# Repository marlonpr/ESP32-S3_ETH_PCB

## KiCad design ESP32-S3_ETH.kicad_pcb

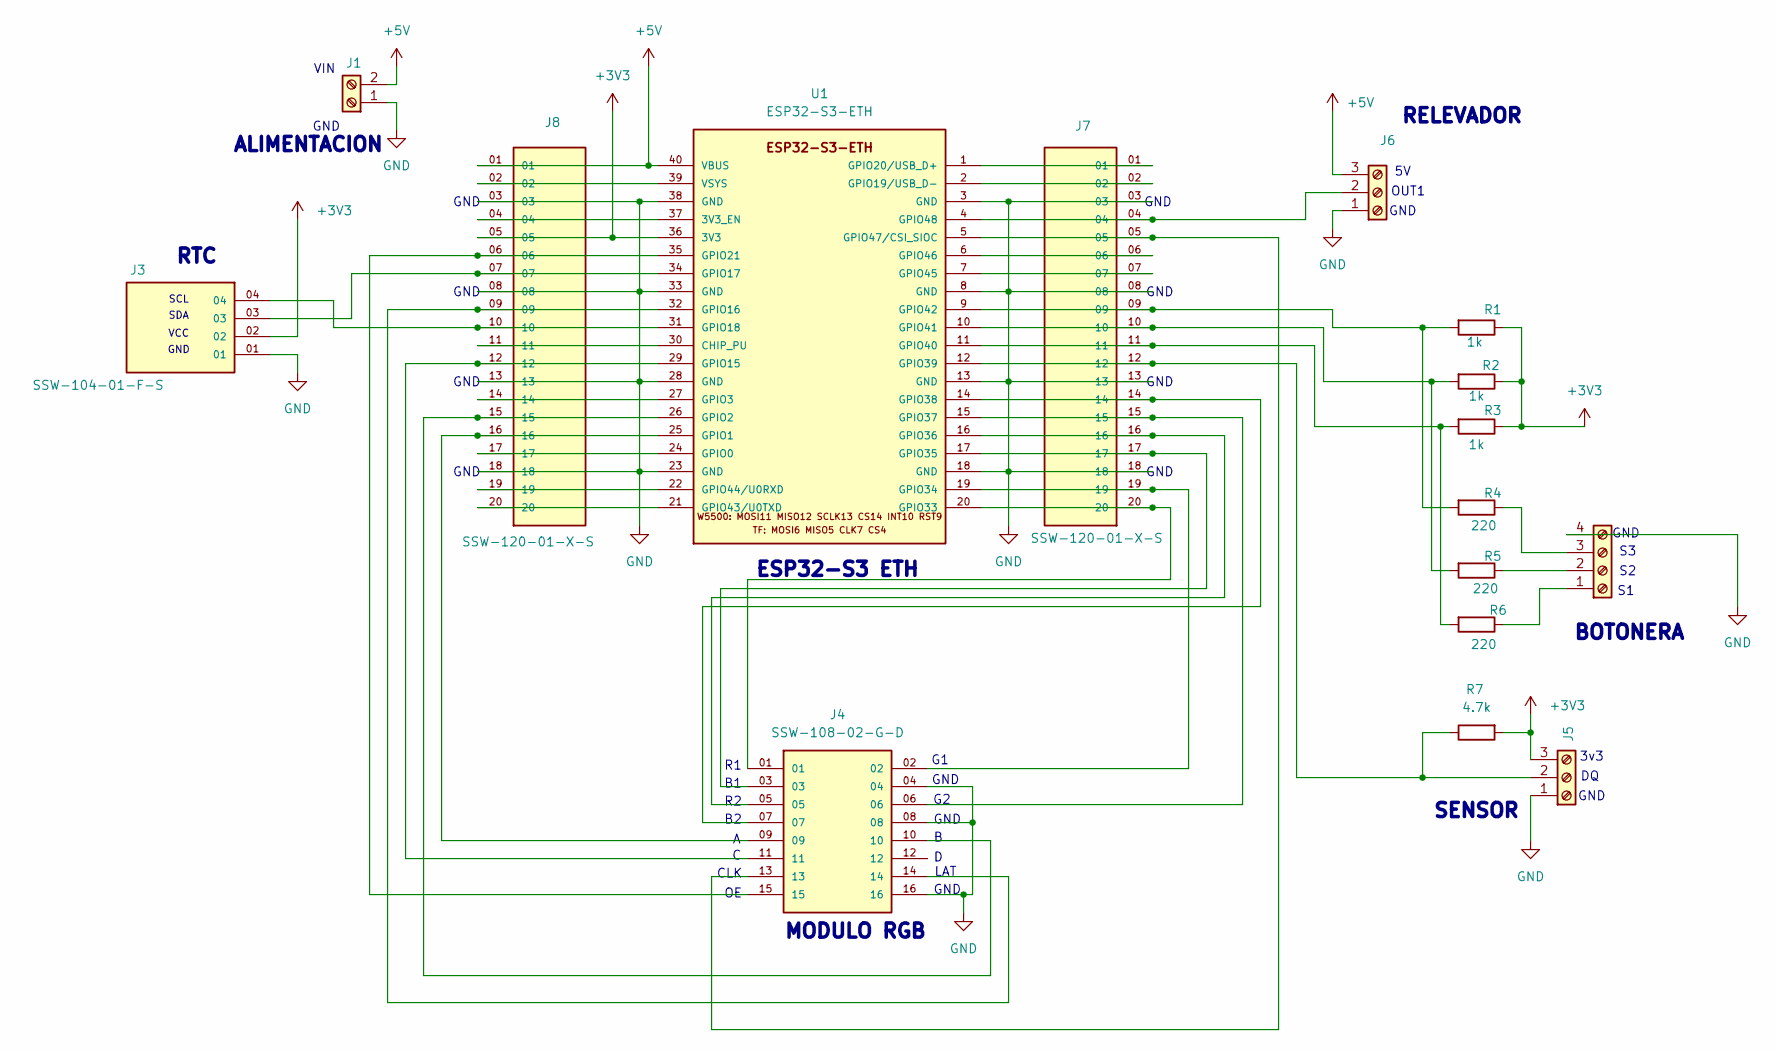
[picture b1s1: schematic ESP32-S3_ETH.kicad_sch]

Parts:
J1: Screw_Terminal_01x02; TerminalBlock_Altech_AK300-2_P5.00mm
J2: Screw_Terminal_01x04; TerminalBlock_Altech_AK300-4_P5.00mm
J3: SSW-104-01-F-S; SAMTEC_SSW-104-01-F-S-RTC; PARTREV R
J4: SSW-108-02-G-D; SAMTEC_SSW-108-02-G-D
J5, J6: Screw_Terminal_01x03; TerminalBlock_Altech_AK300-3_P5.00mm
J7, J8: SSW-120-01-X-S; SAMTEC_SSW-120-01-X-S
R1, R2, R3: 1k; R_Axial_DIN0207_L6.3mm_D2.5mm_P7.62mm_Horizontal
R4, R5, R6: 220; R_Axial_DIN0207_L6.3mm_D2.5mm_P7.62mm_Horizontal
R7: 4.7k; R_Axial_DIN0207_L6.3mm_D2.5mm_P7.62mm_Horizontal
U1: ESP32-S3-ETH; MODULE_ESP32-S3-ETH

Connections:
+3V3: J3.02, J5.3, J8.05, R1.1, R2.1, R3.1, R7.2, U1.36 (3V3)
+5V: J1.2, J6.3, J8.01, U1.40 (VBUS)
GND: J1.1, J2.4, J3.01, J4.04, J4.08, J4.16, J5.1, J6.1, J7.03, J7.08, J7.13, J7.18, J8.03, J8.08, J8.13, J8.18, U1.3 (GND), U1.8 (GND), U1.13 (GND), U1.18 (GND), U1.23 (GND), U1.28 (GND), U1.33 (GND), U1.38 (GND)
unnamed: J2.1, R6.1
unnamed: J2.2, R5.1
unnamed: J2.3, R4.1
unnamed: J5.2, J7.12, R7.1, U1.12 (GPIO39)
unnamed: J6.2, J7.04, U1.4 (GPIO48)
unnamed: J8.04, U1.37 (3V3_EN)
unnamed: J8.11, U1.30 (CHIP_PU)
unnamed: J8.17, U1.24 (GPIO0)
unnamed: J4.09, J8.16, U1.25 (GPIO1)
unnamed: J4.10, J8.15, U1.26 (GPIO2)
unnamed: J8.14, U1.27 (GPIO3)
unnamed: J4.11, J8.12, U1.29 (GPIO15)
unnamed: J4.14, J8.09, U1.32 (GPIO16)
unnamed: J3.03, J8.07, U1.34 (GPIO17)
unnamed: J3.04, J8.10, U1.31 (GPIO18)
unnamed: J7.02, U1.2 (GPIO19/USB_D-)
unnamed: J7.01, U1.1 (GPIO20/USB_D+)
unnamed: J4.15, J8.06, U1.35 (GPIO21)
unnamed: J4.01, J7.20, U1.20 (GPIO33)
unnamed: J4.02, J7.19, U1.19 (GPIO34)
unnamed: J4.03, J7.17, U1.17 (GPIO35)
unnamed: J4.05, J7.16, U1.16 (GPIO36)
unnamed: J4.06, J7.15, U1.15 (GPIO37)
unnamed: J4.07, J7.14, U1.14 (GPIO38)
unnamed: J7.11, R3.2, R6.2, U1.11 (GPIO40)
unnamed: J7.10, R2.2, R5.2, U1.10 (GPIO41)
unnamed: J7.09, R1.2, R4.2, U1.9 (GPIO42)
unnamed: J8.20, U1.21 (GPIO43/U0TXD)
unnamed: J8.19, U1.22 (GPIO44/U0RXD)
unnamed: J7.07, U1.7 (GPIO45)
unnamed: J7.06, U1.6 (GPIO46)
unnamed: J4.13, J7.05, U1.5 (GPIO47/CSI_SIOC)
unnamed: J8.02, U1.39 (VSYS)

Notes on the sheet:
LAT
OUT1
GND
MODULO RGB
BOTONERA
CLK
VCC
SDA
VIN
ESP32-S3 ETH
RTC
ALIMENTACION
SENSOR
RELEVADOR
SCL
3v3

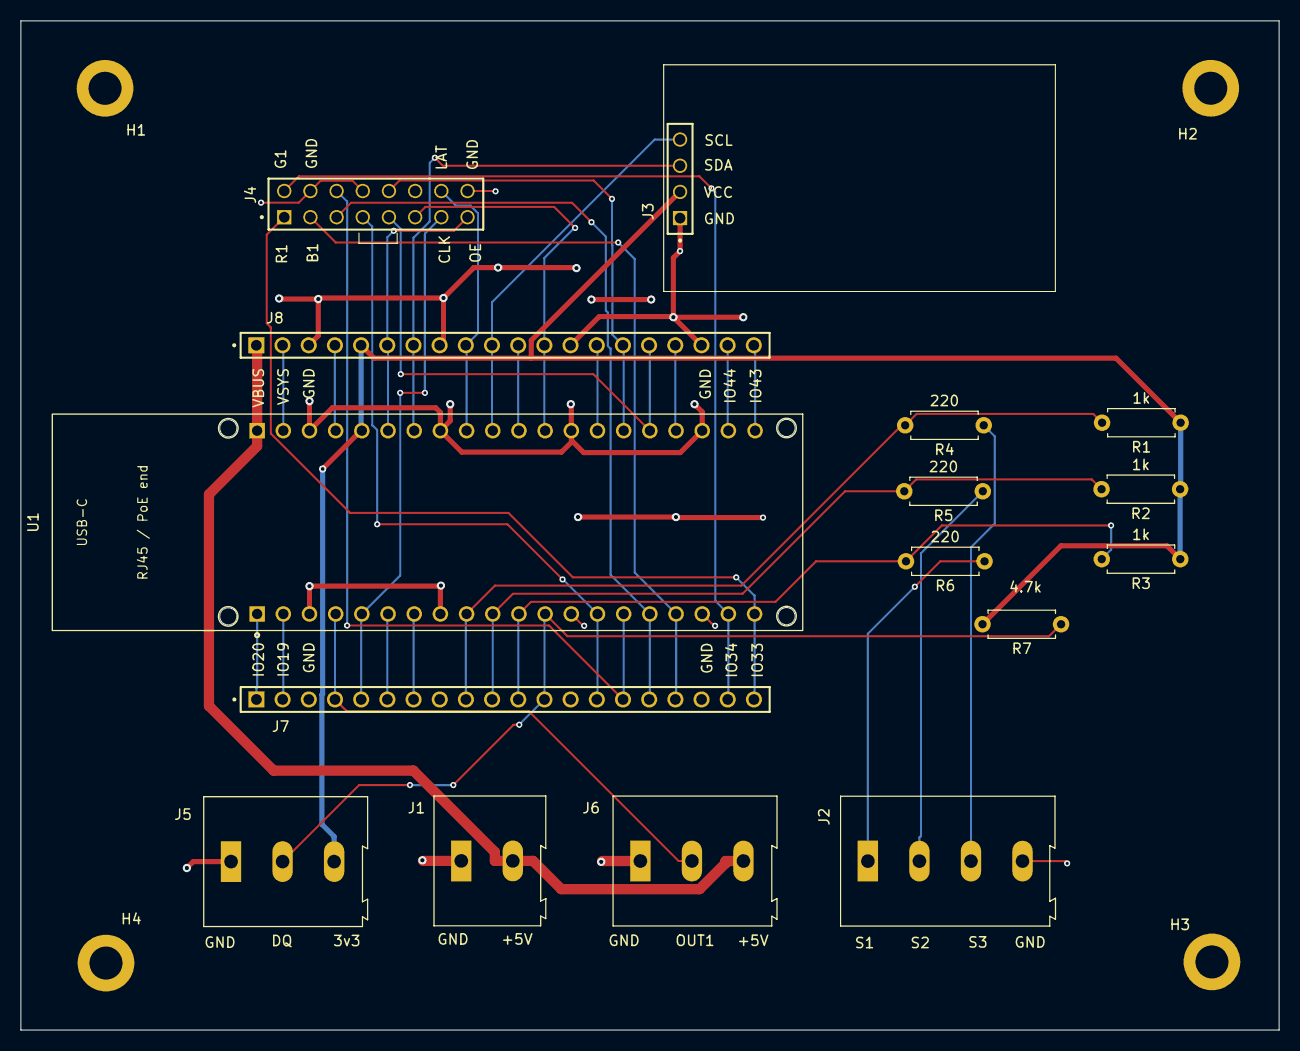
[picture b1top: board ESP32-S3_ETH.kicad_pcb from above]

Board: 2 copper layers, 122.1 x 97.9 mm, 20 parts (0 on the bottom side), 36 nets.

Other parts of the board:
H1, H2, H3, H4: 3.2mm_M3_TH

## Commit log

2026-05-20 S3 symbol and footprint ok
2026-05-20 ssw-120-1 added
2026-05-21 Ground plane and power size trace in process
2026-05-25 v1 ok
2026-05-25 Cleanup track and vias
